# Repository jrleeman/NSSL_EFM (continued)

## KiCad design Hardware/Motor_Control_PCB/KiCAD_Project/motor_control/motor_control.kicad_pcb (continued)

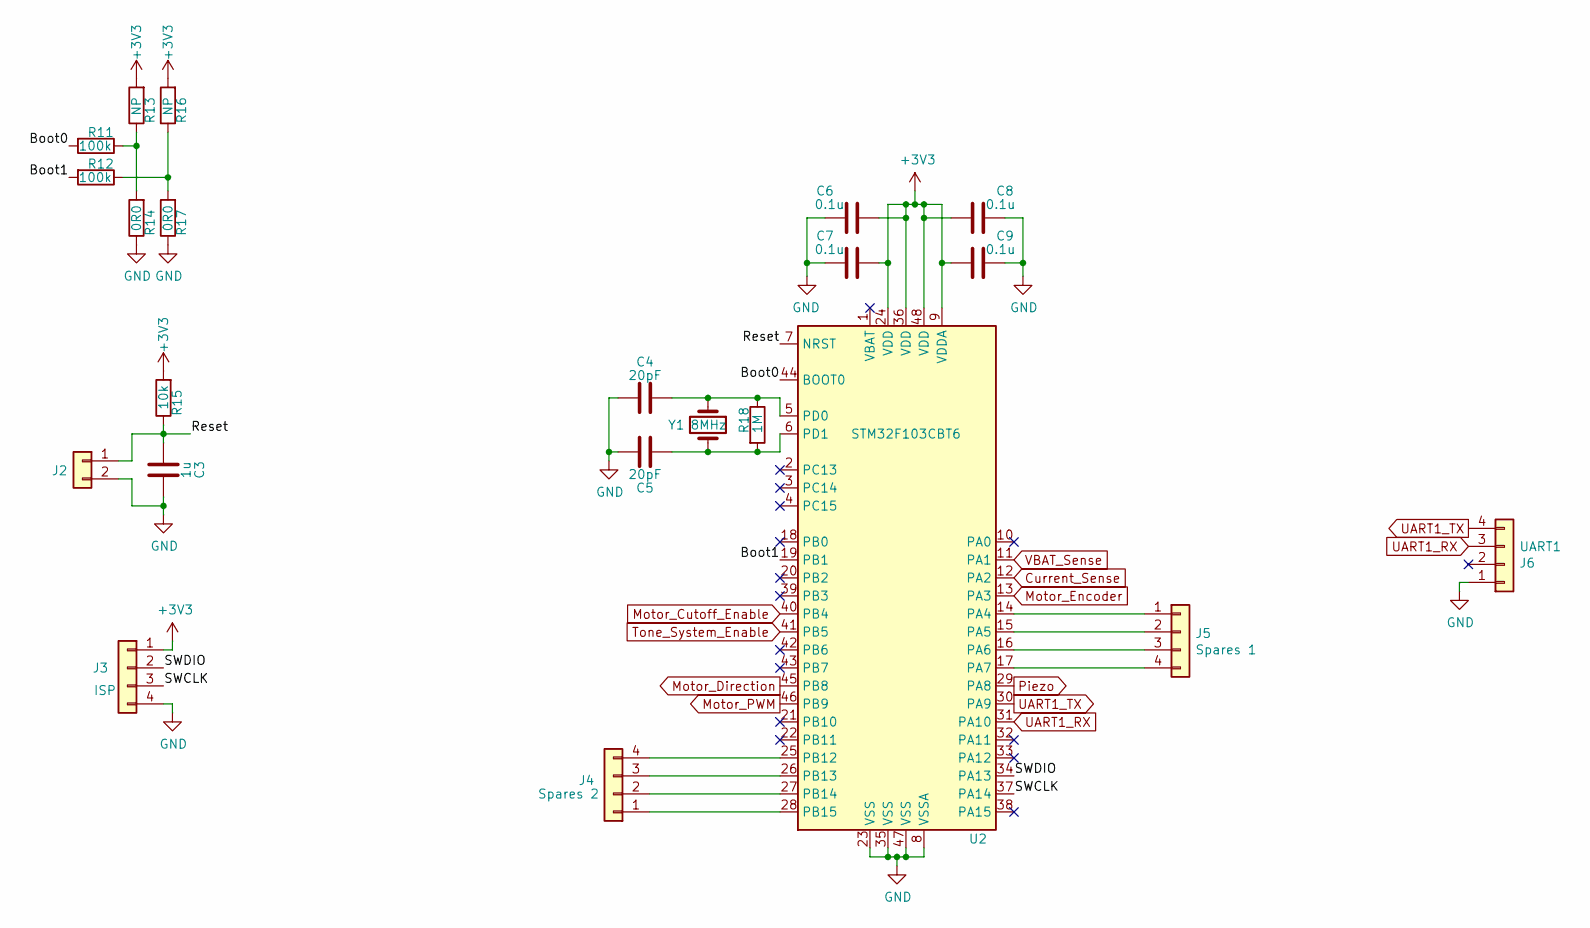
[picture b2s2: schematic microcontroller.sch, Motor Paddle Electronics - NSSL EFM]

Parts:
C3: 1u; C_0603_HandSoldering
C4, C5: 20pF; C_0603_HandSoldering
C6, C7, C8, C9: 0.1u; C_0603_HandSoldering
J2: Conn_01x02; Pin_Header_Straight_1x02_Pitch2.54mm
J3: ISP; Pin_Header_Straight_1x04_Pitch2.54mm
J4: Spares 2; Pin_Header_Straight_1x04_Pitch2.54mm
J5: Spares 1; Pin_Header_Straight_1x04_Pitch2.54mm
J6: UART1; Pin_Header_Straight_1x04_Pitch2.54mm
R11, R12: 100k; R_0603_HandSoldering
R13, R16: NP; R_0603_HandSoldering
R14, R17: 0R0; R_0603_HandSoldering
R15: 10k; R_0603_HandSoldering
R18: 1M; R_0603_HandSoldering
U2: STM32F103CBT6; LQFP-48_7x7mm_Pitch0.5mm
Y1: 8MHz; Crystal_SMD_HC49-SD_HandSoldering

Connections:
+3V3: C6.1, C7.1, C8.1, C9.1, J3.1, R13.2, R15.2, R16.2, U2.9 (VDDA), U2.24 (VDD), U2.36 (VDD), U2.48 (VDD); also elsewhere on the board
/microcontroller/Boot0: R11.2, U2.44 (BOOT0)
/microcontroller/Boot1: R12.2, U2.19 (PB1)
/microcontroller/Reset: C3.2, J2.1, R15.1, U2.7 (NRST)
/microcontroller/SWCLK: J3.3, U2.37 (PA14)
/microcontroller/SWDIO: J3.2, U2.34 (PA13)
Current_Sense: U2.12 (PA2); also elsewhere on the board
GND: C3.1, C4.2, C5.2, C6.2, C7.2, C8.2, C9.2, J2.2, J3.4, J6.1, R14.1, R17.1, U2.8 (VSSA), U2.23 (VSS), U2.35 (VSS), U2.47 (VSS); also elsewhere on the board
Motor_Cutoff_Enable: U2.40 (PB4); also elsewhere on the board
Motor_Direction: U2.45 (PB8); also elsewhere on the board
Motor_Encoder: U2.13 (PA3); also elsewhere on the board
Motor_PWM: U2.46 (PB9); also elsewhere on the board
unnamed: C4.1, R18.1, U2.5 (PD0), Y1.1
unnamed: C5.1, R18.2, U2.6 (PD1), Y1.2
unnamed: J4.1, U2.28 (PB15)
unnamed: J4.2, U2.27 (PB14)
unnamed: J4.3, U2.26 (PB13)
unnamed: J4.4, U2.25 (PB12)
unnamed: J5.1, U2.14 (PA4)
unnamed: J5.2, U2.15 (PA5)
unnamed: J5.3, U2.16 (PA6)
unnamed: J5.4, U2.17 (PA7)
unnamed: R11.1, R13.1, R14.2
unnamed: R12.1, R16.1, R17.2
Piezo: U2.29 (PA8); also elsewhere on the board
Tone_System_Enable: U2.41 (PB5); also elsewhere on the board
UART1_RX: J6.3, U2.31 (PA10)
UART1_TX: J6.4, U2.30 (PA9)
VBAT_Sense: U2.11 (PA1); also elsewhere on the board

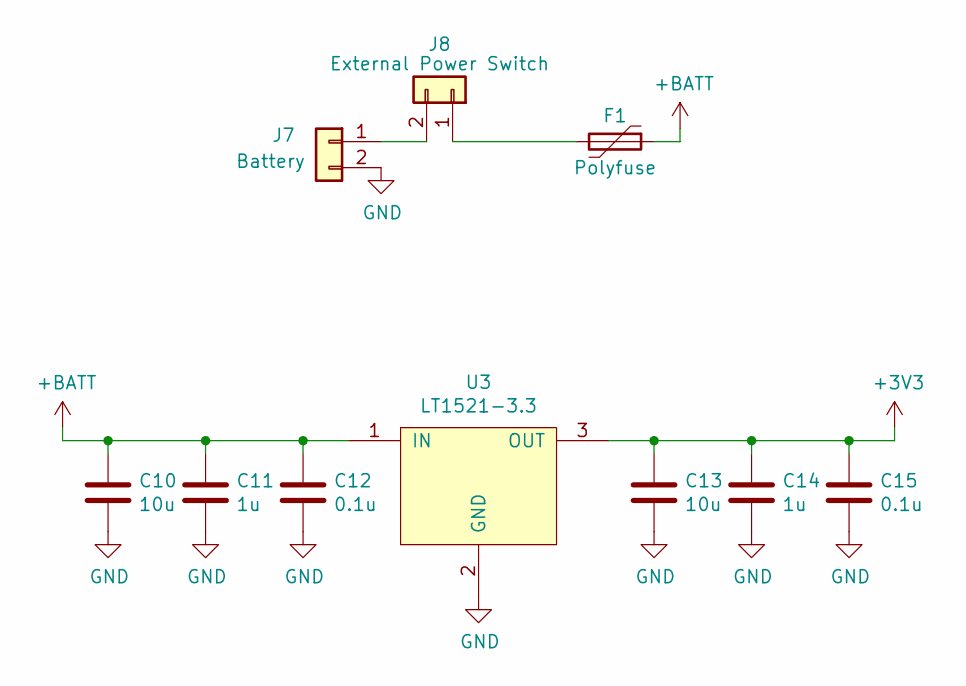
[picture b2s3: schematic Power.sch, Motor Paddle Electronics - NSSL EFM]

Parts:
C10, C13: 10u; C_0603_HandSoldering
C11, C14: 1u; C_0603_HandSoldering
C12, C15: 0.1u; C_0603_HandSoldering
F1: Polyfuse; RGEF250
J7: Battery; Pin_Header_Straight_1x02_Pitch2.54mm
J8: External Power Switch; Pin_Header_Straight_1x02_Pitch2.54mm
U3: LT1521-3.3; SOT-223-3_TabPin2

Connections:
+3V3: C13.1, C14.1, C15.1, U3.3 (OUT); also elsewhere on the board
+BATT: C10.1, C11.1, C12.1, F1.1, U3.1 (IN); also elsewhere on the board
GND: C10.2, C11.2, C12.2, C13.2, C14.2, C15.2, J7.2, U3.2 (GND); also elsewhere on the board
unnamed: F1.2, J8.1
unnamed: J7.1, J8.2

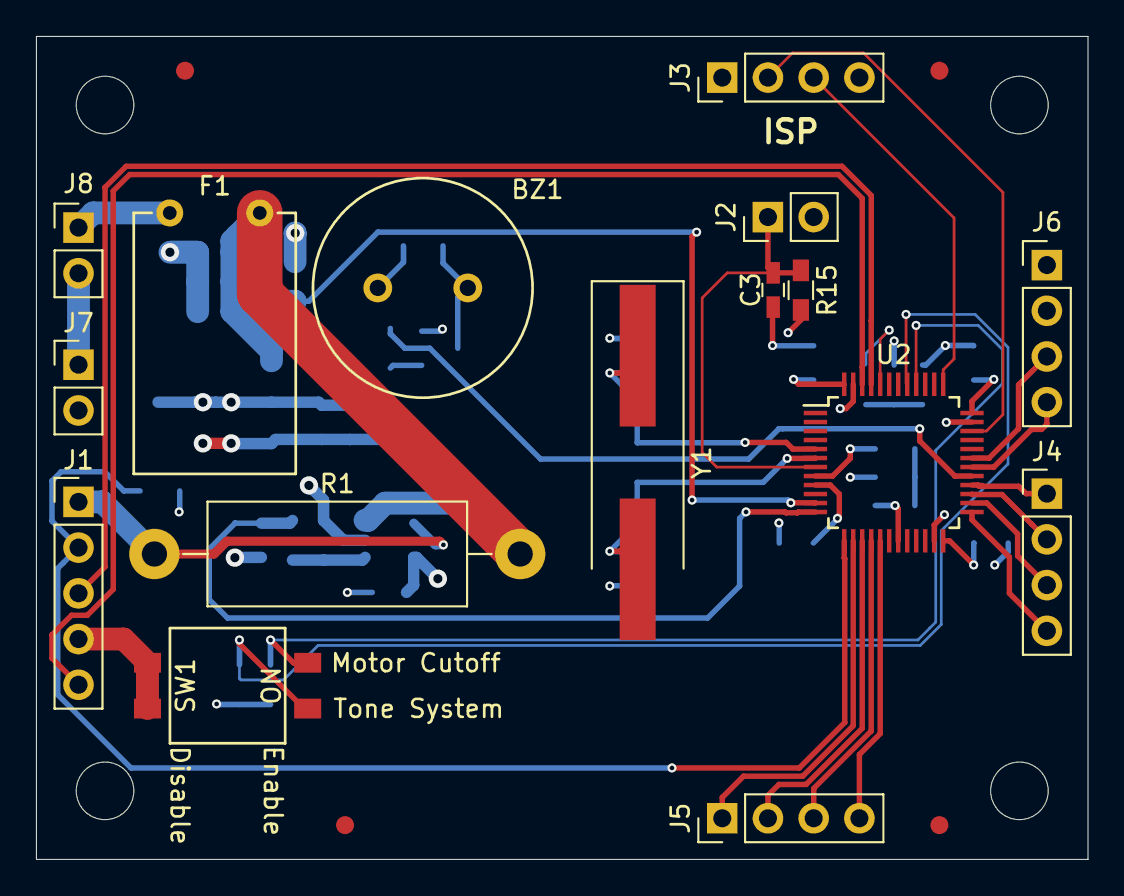
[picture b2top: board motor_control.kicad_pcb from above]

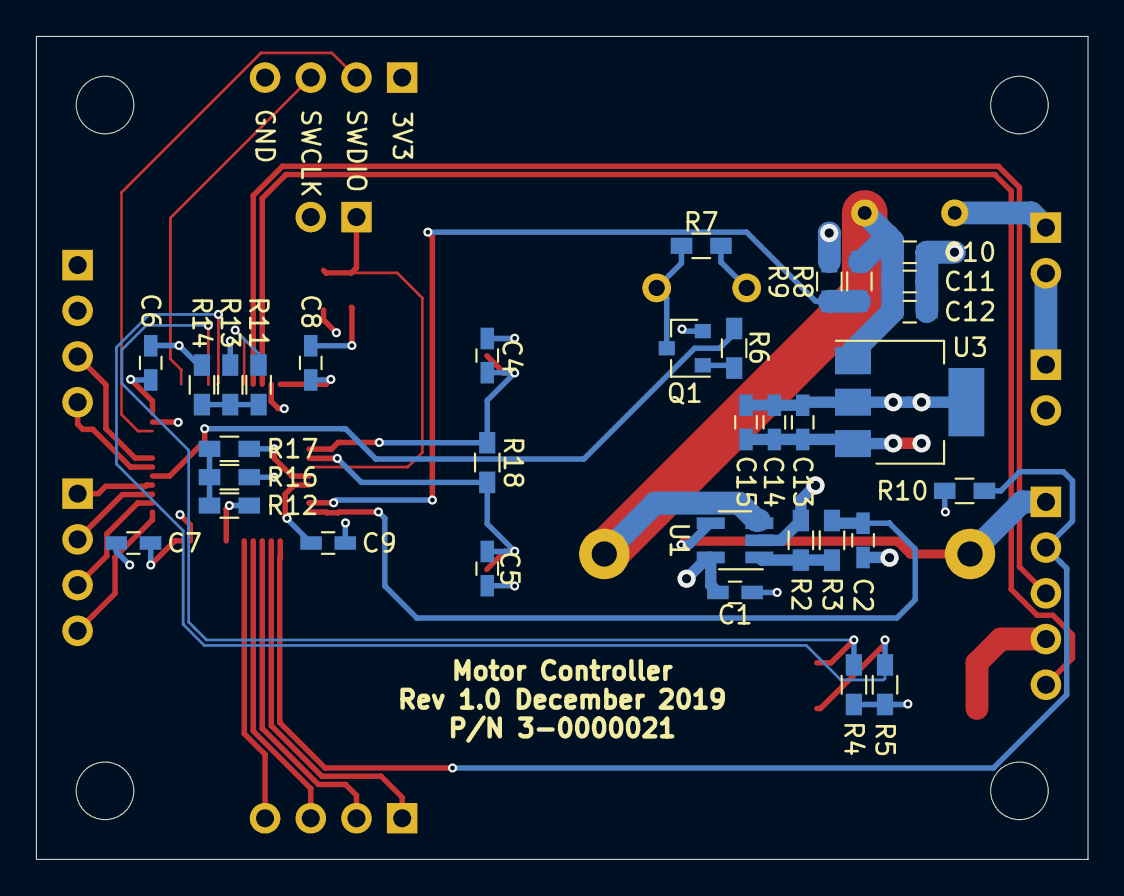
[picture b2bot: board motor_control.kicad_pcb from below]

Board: 4 copper layers, 58.4 x 45.7 mm, 58 parts (33 on the bottom side), 36 nets.

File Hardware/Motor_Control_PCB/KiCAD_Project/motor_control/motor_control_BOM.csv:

Reference, Value, Footprint, Datasheet, Internal Part Number, Populated
"J1","Motor","Pin_Headers:Pin_Header_Straight_1x05_Pitch2.54mm","~","0-0000000","0"
"BZ1","Piezo","lib_fp:PS1240P02BT","~","1-0000443","1"
"U1","INA169","TO_SOT_Packages_SMD:SOT-23-5_HandSoldering","","1-0000452","1"
"C1","0.1u","Capacitors_SMD:C_0603_HandSoldering","~","1-0000007","1"
"R2","10k","Resistors_SMD:R_0603_HandSoldering","~","1-0000010","1"
"R1","1","Resistors_THT:R_Axial_DIN0614_L14.3mm_D5.7mm_P20.32mm_Horizontal","~","1-0000453","1"
"R7","1k","Resistors_SMD:R_0603_HandSoldering","~","1-0000013","1"
"R6","1k","Resistors_SMD:R_0603_HandSoldering","~","1-0000013","1"
"Q1","MMBT3904","TO_SOT_Packages_SMD:SOT-23","https://www.fairchildsemi.com/datasheets/2N/2N3904.pdf","1-0000036","1"
"C2","0.1u","Capacitors_SMD:C_0603_HandSoldering","~","1-0000007","1"
"R3","1M","Resistors_SMD:R_0603_HandSoldering","~","1-0000009","1"
"R10","NP","Resistors_SMD:R_0603_HandSoldering","~","0-0000000","0"
"SW1","Configuration","lib_fp:KAE02LGGR","~","1-0000454","1"
"R4","10k","Resistors_SMD:R_0603_HandSoldering","~","1-0000010","1"
"R5","10k","Resistors_SMD:R_0603_HandSoldering","~","1-0000010","1"
"R8","27k","Resistors_SMD:R_0603_HandSoldering","~","1-0000078","1"
"R9","10k","Resistors_SMD:R_0603_HandSoldering","~","1-0000010","1"
"H1","MountingHole","Mounting_Holes:MountingHole_3.2mm_M3_ISO7380","~","0-0000000","0"
"H2","MountingHole","Mounting_Holes:MountingHole_3.2mm_M3_ISO7380","~","0-0000000","0"
"H3","MountingHole","Mounting_Holes:MountingHole_3.2mm_M3_ISO7380","~","0-0000000","0"
"H4","MountingHole","Mounting_Holes:MountingHole_3.2mm_M3_ISO7380","~","0-0000000","0"
"FID1","Fiducial","Fiducials:Fiducial_1mm_Dia_2.54mm_Outer_CopperTop","~","0-0000000","0"
"FID2","Fiducial","Fiducials:Fiducial_1mm_Dia_2.54mm_Outer_CopperTop","~","0-0000000","0"
"FID3","Fiducial","Fiducials:Fiducial_1mm_Dia_2.54mm_Outer_CopperTop","~","0-0000000","0"
"FID4","Fiducial","Fiducials:Fiducial_1mm_Dia_2.54mm_Outer_CopperTop","~","0-0000000","0"
"U2","STM32F103CBT6","Housings_QFP:LQFP-48_7x7mm_Pitch0.5mm","http://www.st.com/st-web-ui/static/active/en/resource/techni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","1-0000207","1"
"C7","0.1u","Capacitors_SMD:C_0603_HandSoldering","~","1-0000007","1"
"C6","0.1u","Capacitors_SMD:C_0603_HandSoldering","~","1-0000007","1"
"C9","0.1u","Capacitors_SMD:C_0603_HandSoldering","~","1-0000007","1"
"C8","0.1u","Capacitors_SMD:C_0603_HandSoldering","~","1-0000007","1"
"R18","1M","Resistors_SMD:R_0603_HandSoldering","~","1-0000009","1"
"Y1","8MHz","Crystals:Crystal_SMD_HC49-SD_HandSoldering","~","1-0000206","1"
"C4","20pF","Capacitors_SMD:C_0603_HandSoldering","~","1-0000204","1"
"C5","20pF","Capacitors_SMD:C_0603_HandSoldering","~","1-0000204","1"
"J2","Conn_01x02","Pin_Headers:Pin_Header_Straight_1x02_Pitch2.54mm","~","0-0000000","0"
"J6","UART1","Pin_Headers:Pin_Header_Straight_1x04_Pitch2.54mm","~","0-0000000","0"
"J3","ISP","Pin_Headers:Pin_Header_Straight_1x04_Pitch2.54mm","~","0-0000000","0"
"J4","Spares 2","Pin_Headers:Pin_Header_Straight_1x04_Pitch2.54mm","~","0-0000000","0"
"J5","Spares 1","Pin_Headers:Pin_Header_Straight_1x04_Pitch2.54mm","~","0-0000000","0"
"R12","100k","Resistors_SMD:R_0603_HandSoldering","~","1-0000174","1"
"R11","100k","Resistors_SMD:R_0603_HandSoldering","~","1-0000174","1"
"R14","0R0","Resistors_SMD:R_0603_HandSoldering","~","1-0000006","1"
"R17","0R0","Resistors_SMD:R_0603_HandSoldering","~","1-0000006","1"
"R13","NP","Resistors_SMD:R_0603_HandSoldering","~","0-0000000","0"
"R16","NP","Resistors_SMD:R_0603_HandSoldering","~","0-0000000","0"
"R15","10k","Resistors_SMD:R_0603_HandSoldering","~","1-0000010","1"
"C3","1u","Capacitors_SMD:C_0603_HandSoldering","~","1-0000018","1"
"C10","10u","Capacitors_SMD:C_0603_HandSoldering","~","1-0000005","1"
"C11","1u","Capacitors_SMD:C_0603_HandSoldering","~","1-0000018","1"
"C12","0.1u","Capacitors_SMD:C_0603_HandSoldering","~","1-0000007","1"
"U3","LT1521-3.3","TO_SOT_Packages_SMD:SOT-223-3_TabPin2","","1-0000196","1"
"C13","10u","Capacitors_SMD:C_0603_HandSoldering","~","1-0000005","1"
"C14","1u","Capacitors_SMD:C_0603_HandSoldering","~","1-0000018","1"
"C15","0.1u","Capacitors_SMD:C_0603_HandSoldering","~","1-0000007","1"
"J7","Battery","Pin_Headers:Pin_Header_Straight_1x02_Pitch2.54mm","~","0-0000000","0"
"F1","Polyfuse","lib_fp:RGEF250","~","1-0000269","1"
"J8","External Power Switch","Pin_Headers:Pin_Header_Straight_1x02_Pitch2.54mm","~","0-0000000","0"

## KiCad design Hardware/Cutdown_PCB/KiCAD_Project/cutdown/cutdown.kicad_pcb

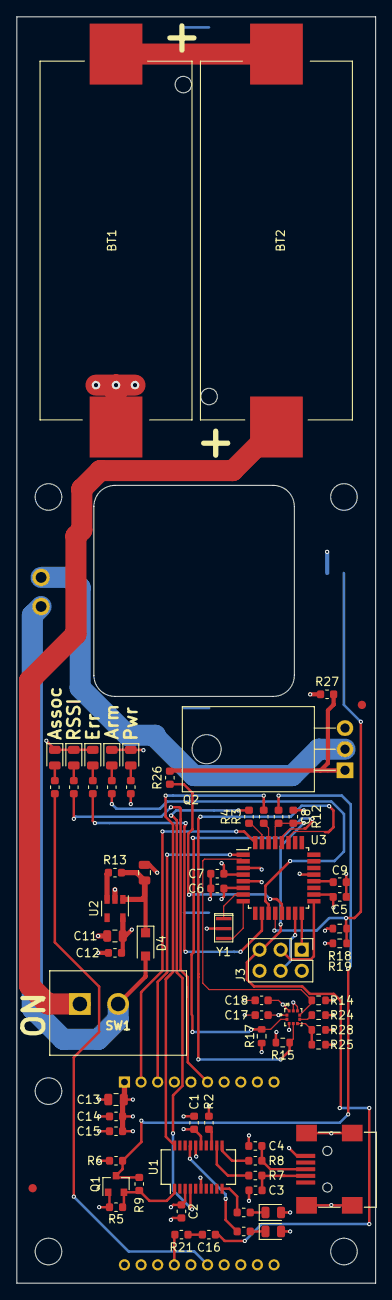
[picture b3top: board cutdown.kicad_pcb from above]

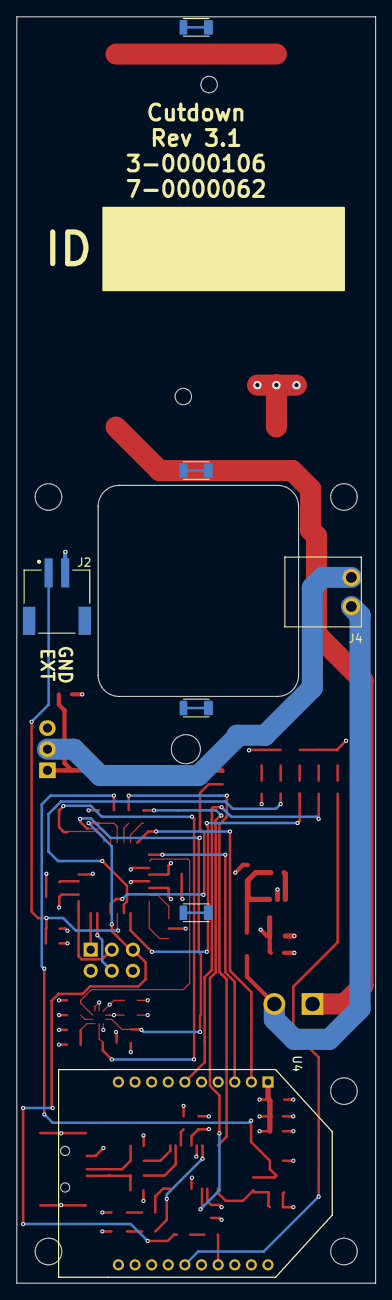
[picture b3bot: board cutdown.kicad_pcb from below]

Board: 4 copper layers, 43.2 x 152.4 mm, 81 parts (7 on the bottom side), 51 nets.

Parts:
BT1, BT2: CR123; 1-0000782
C1, C2, C5, C6, C7, C8, C9, C15, C16: 1-0000007
C3, C4: 1-0000017
C10, C11, C13: 1-0000075
C12, C14: 1-0000018
C17, C18: 0.1u; C_0603_1608Metric
D1: Green; LED_0805_2012Metric
D2, D8: Yellow; LED_0805_2012Metric
D3, D5: Red; LED_0805_2012Metric
D4: D_Schottky; D_SOD-123F
D6: 1-0000601
D7: Blue; LED_0805_2012Metric
FID1, FID2: Fiducial; Fiducial_1mm_Mask2mm
H1, H2, H3, H4, H5: M3_ISO_7380; MountingHole_3.2mm_M3_ISO7380
J1: Mini_USB_B; MiniUSB
J2: External Cutdown; JST_S2B-PH-SM4-TB(LF)(SN)
J3: ISP; PinHeader_2x03_P2.54mm_Vertical
J4: Hot Wire; 1-0000783
PCB1: barepcb
Q1: 2N7002; SOT-23
Q2: FQP30N06L; TO-220-3_Horizontal_TabDown
R1, R10, R11, R16, R20, R22, R23: 1-0000008
R2, R9, R21, R26: 1-0000006
R3, R4: 1-0000013
R5, R6, R12, R27: 1-0000010
R7, R8: 1-0000012
R13: 1-0000174
R14, R15, R17, R18, R24, R28: 10k; R_0603_1608Metric
R19, R25: NP; R_0603_1608Metric
SW1: SW_SPST; SW_GF-123-0054
TP1, TP2, TP3, TP4: 1-0000952
U1: FT231XS; SSOP-20_3.9x8.7mm_P0.635mm
U2: SPX3819M5-L-3-3; SOT-23-5
U3: ATmega328P-AU; TQFP-32_7x7mm_P0.8mm
U4: XBee
U5: BMP388; PQFN50P200X200X80-10N
Y1: 8MHz; Resonator

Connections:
+3V3: C1.1, C2.1, C5.1, C6.1, C7.1, C11.1, C12.1, C13.1, C14.1, C15.1, C17.1, C18.2, D2.2, D3.2, J3.2, Q1.1, R1.2, R2.2, R5.2, R6.2, R12.1, R14.1, R15.1, R17.1, R18.1, R24.1, R25.1, U1.3, U1.15, U2.5, U3.4, U3.6, U3.18, U4.1, U5.1, U5.10
+BATT: C10.1, D4.1, R13.1, U2.1
BMP388_INT: R14.2, U3.2, U5.7
Cutdown_Command: R26.2, U3.13
DTR: C8.2, Q1.3, R6.1, R9.2
EXT_CUTDOWN: J2.1, R18.2, R19.2, U3.12
GND: BT1.2, C1.2, C2.2, C3.2, C4.2, C5.2, C6.2, C7.2, C9.2, C10.2, C11.2, C12.2, C13.2, C14.2, C15.2, C17.2, C18.1, D1.1, D5.1, D6.1, D7.1, D8.1, J1.5, J1.6, J1.7, J1.8, J1.9, J2.2, J3.6, Q2.3, R19.1, R27.2, R28.2, U1.6, U1.16, U2.2, U3.3, U3.5, U3.21, U4.10, U5.3, U5.8, U5.9, Y1.2
MISO: J3.1, U3.16
MOSI: J3.4, U3.15
unnamed: BT1.1, BT2.2
unnamed: BT2.1, SW1.1
unnamed: C3.1, J1.2, R7.2
unnamed: C4.1, J1.3, R8.2
unnamed: C9.1, U3.20
unnamed: C16.1, R21.2
unnamed: D1.2, R1.1
unnamed: D2.1, R10.1
unnamed: D3.1, R11.1
unnamed: D5.2, R16.1
unnamed: D6.2, R20.1
unnamed: D7.2, R22.2
unnamed: D8.2, R23.1
unnamed: J4.2, Q2.2
unnamed: Q1.2, R5.1, R9.1, U1.1
unnamed: Q2.1, R26.1, R27.1
unnamed: R2.1, U1.13
unnamed: R3.2, U1.20
unnamed: R4.2, U1.4
unnamed: R7.1, U1.12
unnamed: R8.1, U1.11
unnamed: R10.2, U1.17
unnamed: R11.2, U1.10
unnamed: R13.2, U2.3
unnamed: R16.2, U3.10
unnamed: R20.2, U3.11
unnamed: R21.1, U4.17
unnamed: R22.1, U4.6
unnamed: R23.2, U4.15
unnamed: R24.2, U5.6
unnamed: R25.2, R28.1, U5.5
unnamed: U3.7, Y1.1
unnamed: U3.8, Y1.3
RESET: C8.1, C16.2, J3.5, R12.2, U3.29
RXI: R3.1, U3.30
SCK: J3.3, U3.17
SCL: R17.2, U3.28, U5.2
SDA: R15.2, U3.27, U5.4
SW_PWR: D4.2, J4.1, SW1.2
TXO: R4.1, U3.31
XBee_from_uC: U3.1, U4.3
XBee_to_uC: U3.32, U4.2

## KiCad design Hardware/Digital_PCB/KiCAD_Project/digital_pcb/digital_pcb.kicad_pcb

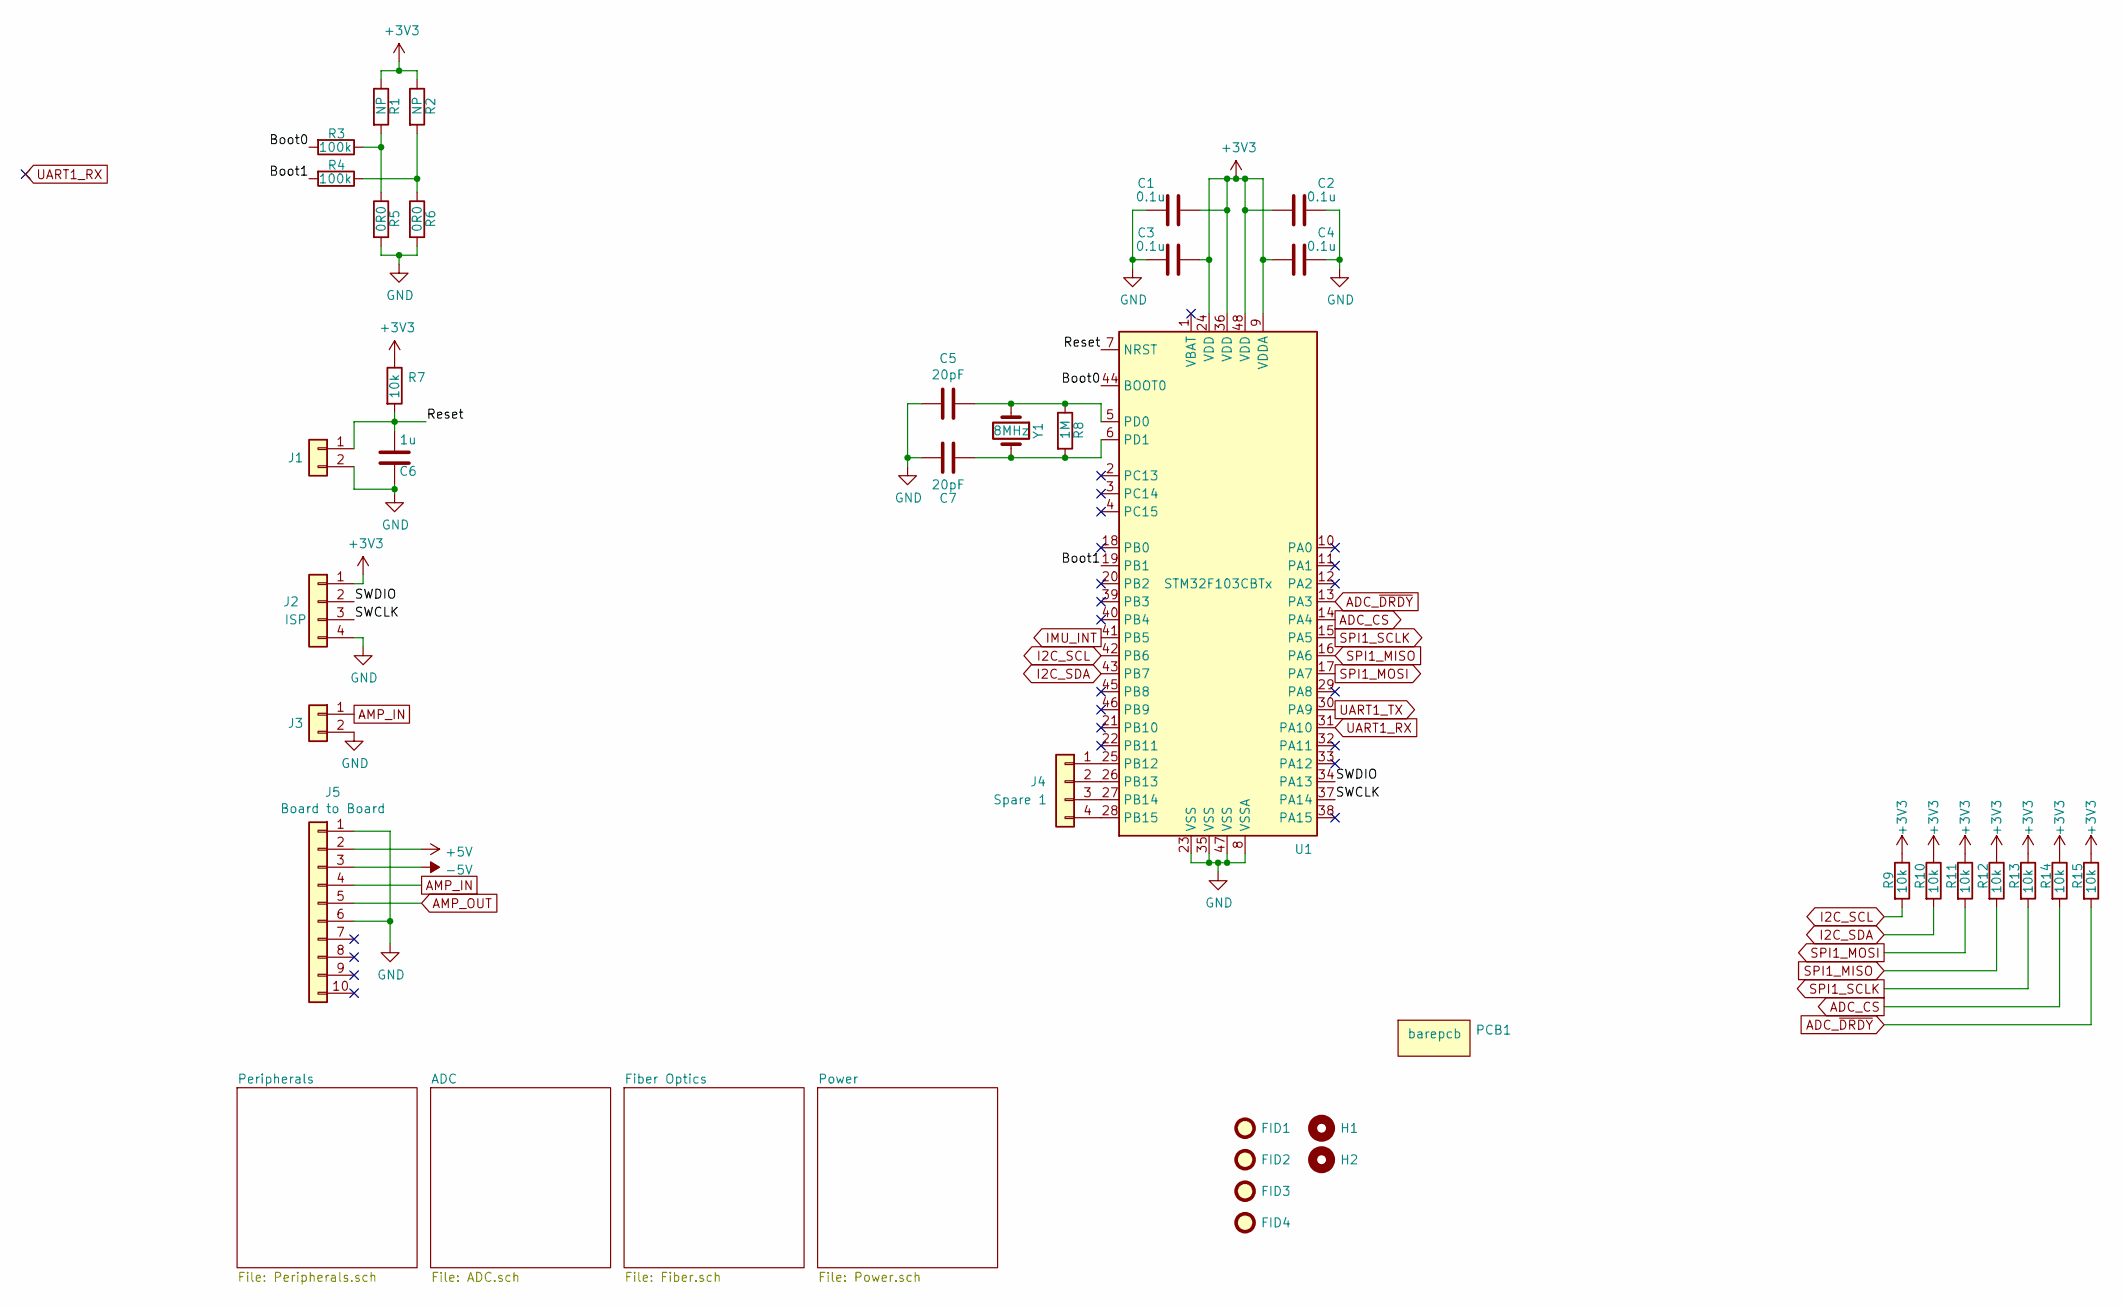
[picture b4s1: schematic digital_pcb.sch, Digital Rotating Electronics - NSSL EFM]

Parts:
C1, C2, C3, C4: 0.1u; C_0603_1608Metric
C5, C7: 20pF; C_0603_1608Metric
C6: 1u; C_0603_1608Metric
FID1, FID2, FID3, FID4: Fiducial; Fiducial_1mm_Dia_2mm_Outer
H1, H2: MountingHole; MountingHole_3.2mm_M3_ISO7380
J1, J3: Conn_01x02; PinHeader_1x02_P2.54mm_Vertical
J2: ISP; PinHeader_1x04_P2.54mm_Vertical
J4: Spare 1; PinHeader_1x04_P2.54mm_Vertical
J5: Board to Board; PinHeader_1x10_P2.54mm_Vertical
PCB1: barepcb
R1, R2: NP; R_0603_1608Metric
R3, R4: 100k; R_0603_1608Metric
R5, R6: 0R0; R_0603_1608Metric
R7, R9, R10, R11, R12, R13, R14, R15: 10k; R_0603_1608Metric
R8: 1M; R_0603_1608Metric
U1: STM32F103CBTx; LQFP-48_7x7mm_Pitch0.5mm
Y1: 8MHz; Crystal_SMD_HC49-SD

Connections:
+3V3: C1.1, C2.1, C3.1, C4.1, J2.1, R1.1, R2.1, R7.1, R9.1, R10.1, R11.1, R12.1, R13.1, R14.1, R15.1, U1.9 (VDDA), U1.24 (VDD), U1.36 (VDD), U1.48 (VDD); also elsewhere on the board
+5V: J5.2; also elsewhere on the board
-5V: J5.3; also elsewhere on the board
/Boot0: R3.2, U1.44 (BOOT0)
/Boot1: R4.2, U1.19 (PB1)
/Reset: C6.2, J1.1, R7.2, U1.7 (NRST)
/SWCLK: J2.3, U1.37 (PA14)
/SWDIO: J2.2, U1.34 (PA13)
ADC_CS: R14.2, U1.14 (PA4); also elsewhere on the board
ADC_~DRDY: R15.2, U1.13 (PA3); also elsewhere on the board
AMP_IN: J3.1, J5.4
AMP_OUT: J5.5; also elsewhere on the board
GND: C1.2, C2.2, C3.2, C4.2, C5.2, C6.1, C7.2, J1.2, J2.4, J3.2, J5.1, J5.6, R5.2, R6.2, U1.8 (VSSA), U1.23 (VSS), U1.35 (VSS), U1.47 (VSS); also elsewhere on the board
I2C_SCL: R9.2, U1.42 (PB6); also elsewhere on the board
I2C_SDA: R10.2, U1.43 (PB7); also elsewhere on the board
IMU_INT: U1.41 (PB5); also elsewhere on the board
unnamed: C5.1, R8.1, U1.5 (PD0), Y1.1
unnamed: C7.1, R8.2, U1.6 (PD1), Y1.2
unnamed: J4.1, U1.25 (PB12)
unnamed: J4.2, U1.26 (PB13)
unnamed: J4.3, U1.27 (PB14)
unnamed: J4.4, U1.28 (PB15)
unnamed: R1.2, R3.1, R5.1
unnamed: R2.2, R4.1, R6.1
SPI1_MISO: R12.2, U1.16 (PA6); also elsewhere on the board
SPI1_MOSI: R11.2, U1.17 (PA7); also elsewhere on the board
SPI1_SCLK: R13.2, U1.15 (PA5); also elsewhere on the board
UART1_TX: U1.30 (PA9); also elsewhere on the board

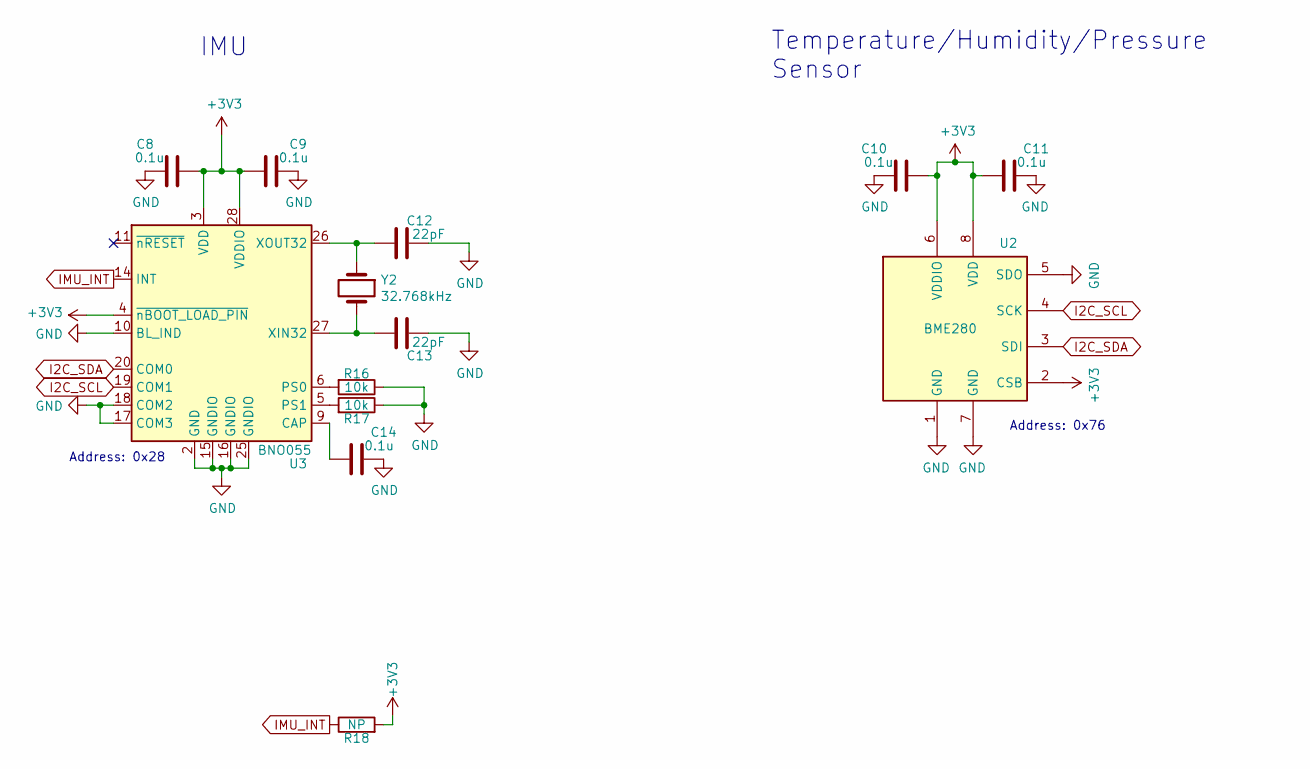
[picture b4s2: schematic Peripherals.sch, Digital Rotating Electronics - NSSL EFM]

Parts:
C8, C9, C10, C11, C14: 0.1u; C_0603_1608Metric
C12, C13: 22pF; C_0603_1608Metric
R16, R17: 10k; R_0603_1608Metric
R18: NP; R_0603_1608Metric
U2: BME280; Bosch_LGA-8_2.5x2.5mm_P0.65mm_ClockwisePinNumbering
U3: BNO055; LGA28R50P4X10_380X520X100
Y2: 32.768kHz; 4-SOJ

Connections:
+3V3: C8.1, C9.1, C10.1, C11.1, R18.2, U2.2 (CSB), U2.6 (VDDIO), U2.8 (VDD), U3.3 (VDD), U3.4 (~nBOOT_LOAD_PIN), U3.28 (VDDIO); also elsewhere on the board
GND: C8.2, C9.2, C10.2, C11.2, C12.1, C13.1, C14.2, R16.1, R17.1, U2.1 (GND), U2.5 (SDO), U2.7 (GND), U3.2 (GND), U3.10 (BL_IND), U3.15 (GNDIO), U3.16 (GNDIO), U3.17 (COM3), U3.18 (COM2), U3.25 (GNDIO); also elsewhere on the board
I2C_SCL: U2.4 (SCK), U3.19 (COM1); also elsewhere on the board
I2C_SDA: U2.3 (SDI), U3.20 (COM0); also elsewhere on the board
IMU_INT: R18.1, U3.14 (INT); also elsewhere on the board
unnamed: C12.2, U3.26 (XOUT32), Y2.1
unnamed: C13.2, U3.27 (XIN32), Y2.2
unnamed: C14.1, U3.9 (CAP)
unnamed: R16.2, U3.6 (PS0)
unnamed: R17.2, U3.5 (PS1)

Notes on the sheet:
Temperature/Humidity/Pressure Sensor
IMU
Address: 0x76
Address: 0x28

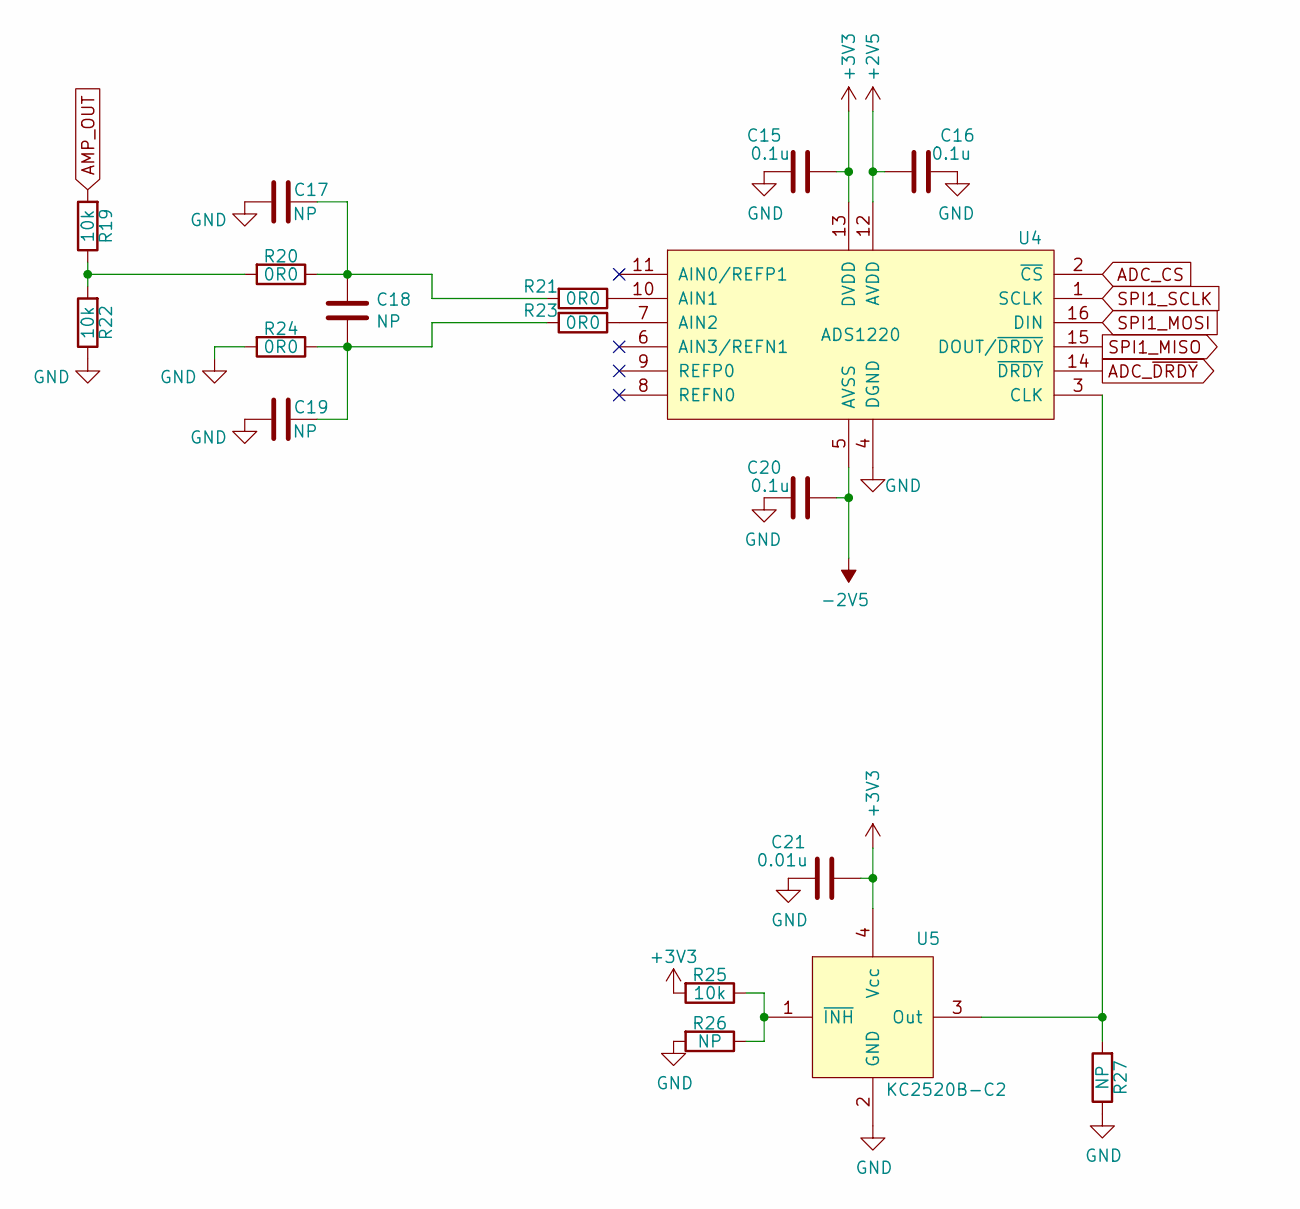
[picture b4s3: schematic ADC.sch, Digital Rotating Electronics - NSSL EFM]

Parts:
C15, C16, C20: 0.1u; C_0603_1608Metric
C17, C18, C19: NP; C_0603_1608Metric
C21: 0.01u; C_0603_1608Metric
R19, R22, R25: 10k; R_0603_1608Metric
R20, R21, R23, R24: 0R0; R_0603_1608Metric
R26, R27: NP; R_0603_1608Metric
U4: ADS1220; TSSOP-16_4.4x5mm_Pitch0.65mm
U5: KC2520B-C2

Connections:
+2V5: C16.1, U4.12 (AVDD); also elsewhere on the board
+3V3: C15.1, C21.1, R25.2, U4.13 (DVDD), U5.4 (Vcc); also elsewhere on the board
-2V5: C20.1, U4.5 (AVSS); also elsewhere on the board
ADC_CS: U4.2 (~CS); also elsewhere on the board
ADC_~DRDY: U4.14 (~DRDY); also elsewhere on the board
AMP_OUT: R19.2; also elsewhere on the board
GND: C15.2, C16.2, C17.2, C19.2, C20.2, C21.2, R22.1, R24.2, R26.2, R27.1, U4.4 (DGND), U5.2 (GND); also elsewhere on the board
unnamed: C17.1, C18.1, R20.1, R21.2
unnamed: C18.2, C19.1, R23.2, R24.1
unnamed: R19.1, R20.2, R22.2
unnamed: R21.1, U4.10 (AIN1)
unnamed: R23.1, U4.7 (AIN2)
unnamed: R25.1, R26.1, U5.1 (~INH)
unnamed: R27.2, U4.3 (CLK), U5.3 (Out)
SPI1_MISO: U4.15 (DOUT/~DRDY); also elsewhere on the board
SPI1_MOSI: U4.16 (DIN); also elsewhere on the board
SPI1_SCLK: U4.1 (SCLK); also elsewhere on the board

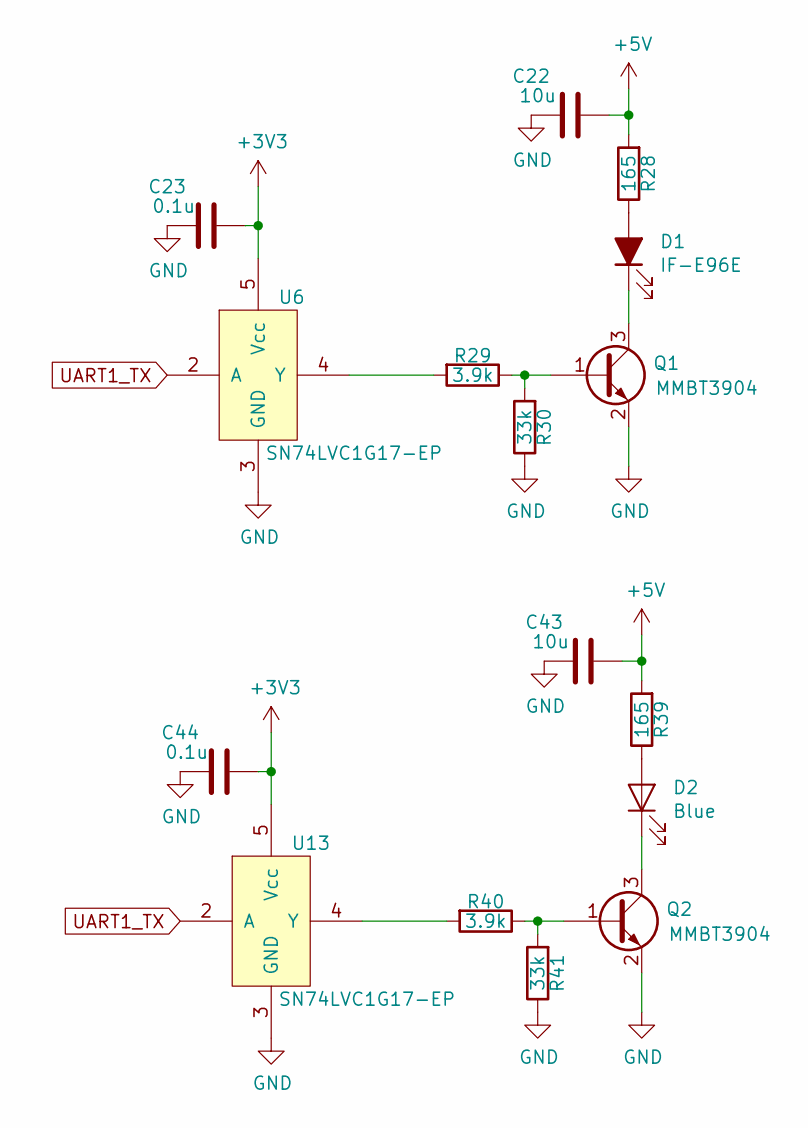
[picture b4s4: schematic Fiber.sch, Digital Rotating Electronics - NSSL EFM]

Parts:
C22, C43: 10u; C_0805_2012Metric
C23, C44: 0.1u; C_0603_1608Metric
D1: IF-E96E; IF_E96E
D2: 1-0000599
Q1, Q2: 1-0000036
R28, R39: 165; R_1206_3216Metric
R29, R40: 3.9k; R_0603_1608Metric
R30, R41: 33k; R_0603_1608Metric
U6, U13: SN74LVC1G17-EP; SOT-23-5_HandSoldering

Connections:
+3V3: C23.1, C44.1, U6.5 (Vcc), U13.5 (Vcc); also elsewhere on the board
+5V: C22.1, C43.1, R28.2, R39.2; also elsewhere on the board
GND: C22.2, C23.2, C43.2, C44.2, Q1.2 (E), Q2.2 (E), R30.1, R41.1, U6.3 (GND), U13.3 (GND); also elsewhere on the board
unnamed: D1.1 (K), Q1.3 (C)
unnamed: D1.2 (A), R28.1
unnamed: D2.1 (K), Q2.3 (C)
unnamed: D2.2 (A), R39.1
unnamed: Q1.1 (B), R29.1, R30.2
unnamed: Q2.1 (B), R40.1, R41.2
unnamed: R29.2, U6.4 (Y)
unnamed: R40.2, U13.4 (Y)
UART1_TX: U6.2 (A), U13.2 (A); also elsewhere on the board

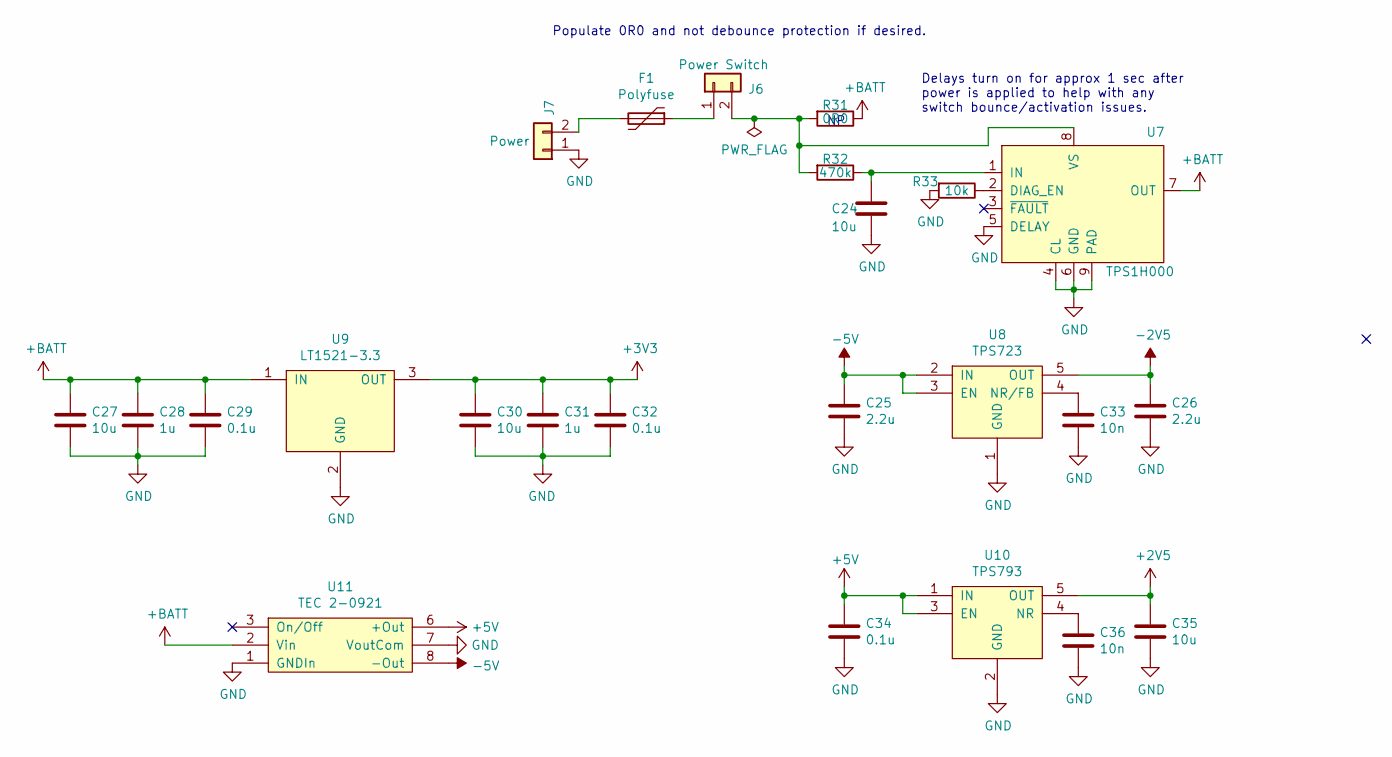
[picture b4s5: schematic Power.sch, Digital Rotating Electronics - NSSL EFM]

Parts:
C24, C27, C30, C35: 10u; C_0805_2012Metric
C25, C26: 2.2u; C_0603_1608Metric
C28, C31: 1u; C_0603_1608Metric
C29, C32, C34: 0.1u; C_0603_1608Metric
C33, C36: 10n; C_0603_1608Metric
F1: Polyfuse; RGEF250
J6: Power Switch; PinHeader_1x02_P2.54mm_Vertical
J7: Power; PinHeader_1x02_P2.54mm_Vertical
R31: 0R0; R_0603_1608Metric
R32: 470k; R_0603_1608Metric
R33: 10k; R_0603_1608Metric
U7: TPS1H000; MSOP-8-1EP_3x3mm_P0.65mm_EP1.95x2.15mm
U8: TPS723; SOT-23-5_HandSoldering
U9: LT1521-3.3; SOT-223-3_TabPin2
U10: TPS793; SOT-23-5_HandSoldering
U11: TEC 2-0921; TEC2

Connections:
+2V5: C35.1, U10.5 (OUT); also elsewhere on the board
+3V3: C30.1, C31.1, C32.1, U9.3 (OUT); also elsewhere on the board
+5V: C34.1, U10.1 (IN), U10.3 (EN), U11.6 (+Out); also elsewhere on the board
+BATT: C27.1, C28.1, C29.1, R31.1, U7.7 (OUT), U9.1 (IN), U11.2 (Vin)
-2V5: C26.1, U8.5 (OUT); also elsewhere on the board
-5V: C25.1, U8.2 (IN), U8.3 (EN), U11.8 (-Out); also elsewhere on the board
GND: C24.2, C25.2, C26.2, C27.2, C28.2, C29.2, C30.2, C31.2, C32.2, C33.2, C34.2, C35.2, C36.2, J7.1, R33.2, U7.4 (CL), U7.5 (DELAY), U7.6 (GND), U7.9 (PAD), U8.1 (GND), U9.2 (GND), U10.2 (GND), U11.1 (GNDIn), U11.7 (VoutCom); also elsewhere on the board
unnamed: C24.1, R32.1, U7.1 (IN)
unnamed: C33.1, U8.4 (NR/FB)
unnamed: C36.1, U10.4 (NR)
unnamed: F1.1, J6.1
unnamed: F1.2, J7.2
unnamed: J6.2, R31.2, R32.2, U7.8 (VS)
unnamed: R33.1, U7.2 (DIAG_EN)

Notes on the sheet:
Populate 0R0 and not debounce protection if desired.
Delays turn on for approx 1 sec after power is applied to help with any switch bounce/activation issues.
